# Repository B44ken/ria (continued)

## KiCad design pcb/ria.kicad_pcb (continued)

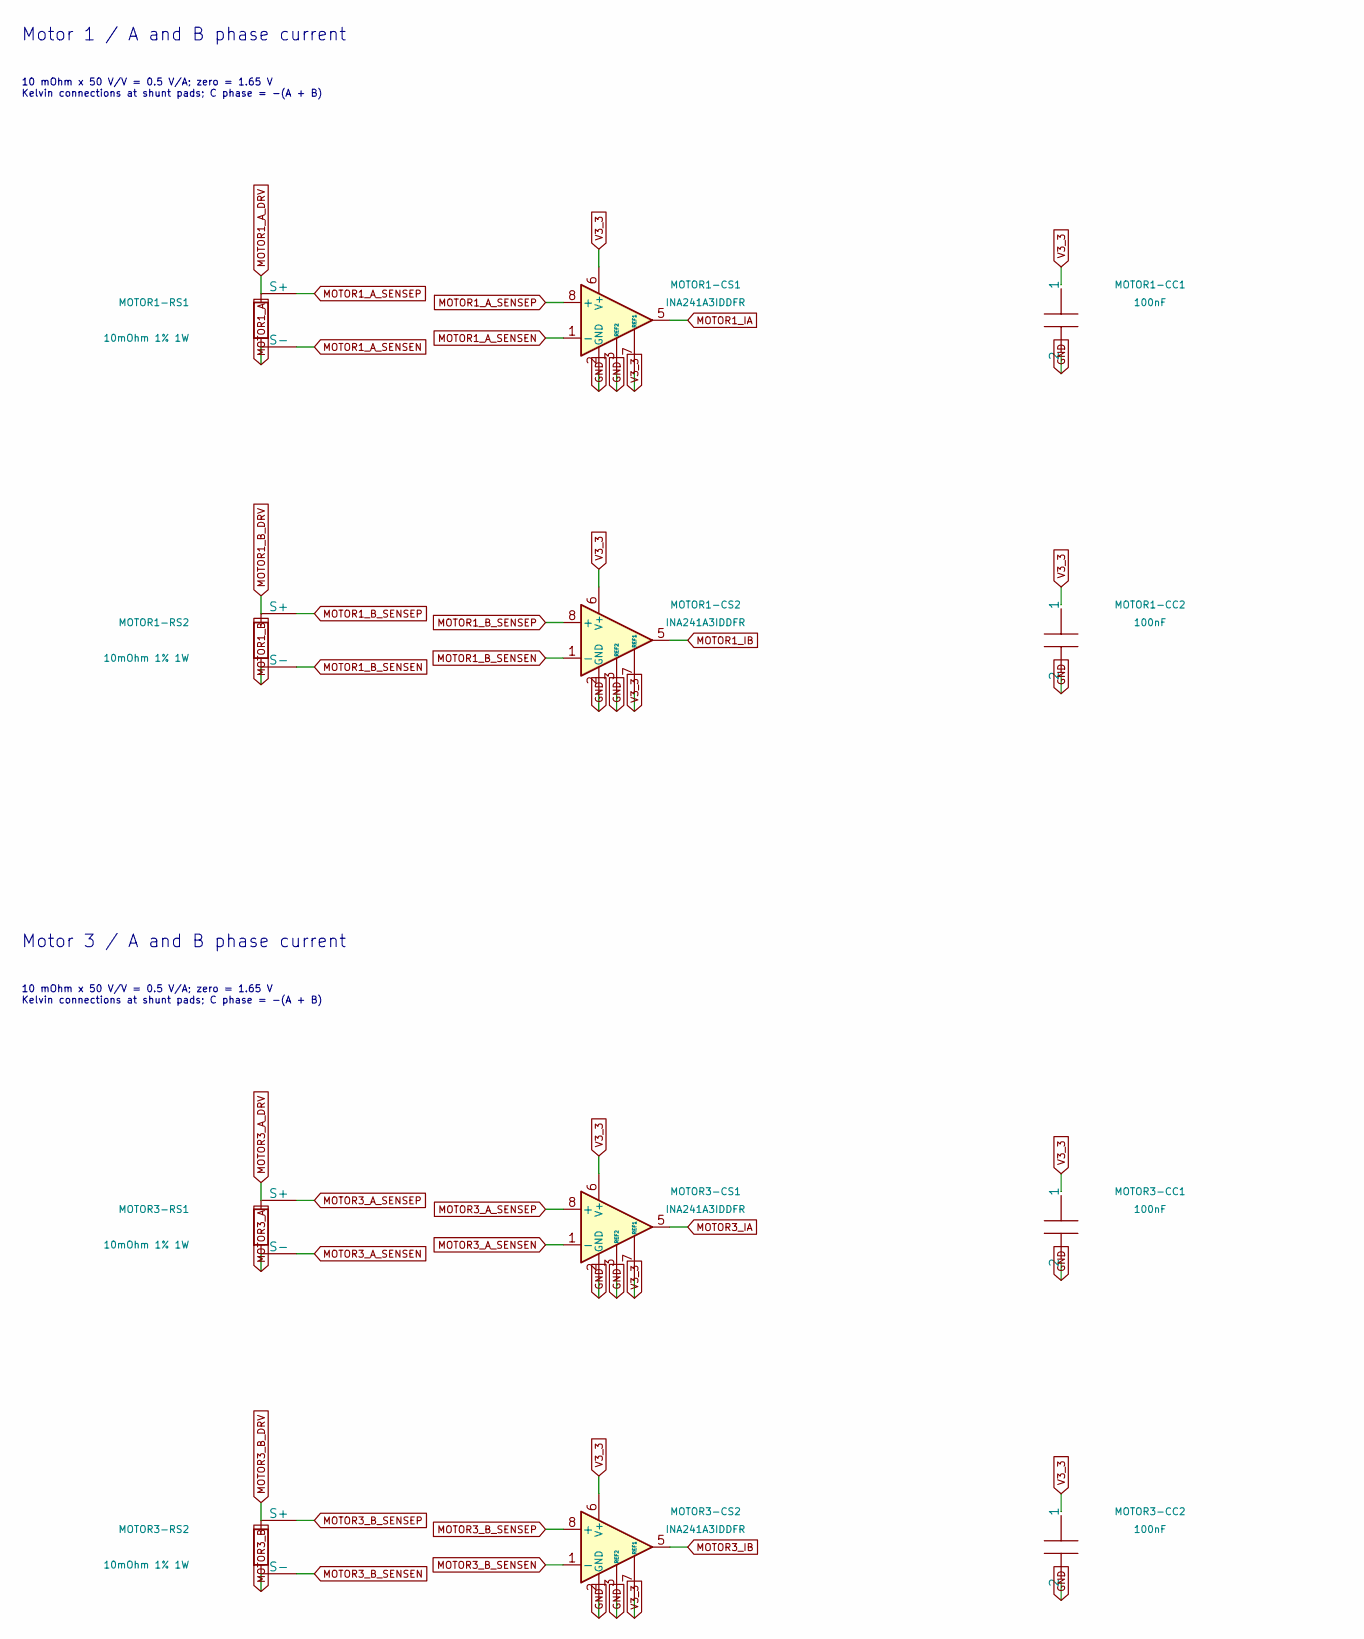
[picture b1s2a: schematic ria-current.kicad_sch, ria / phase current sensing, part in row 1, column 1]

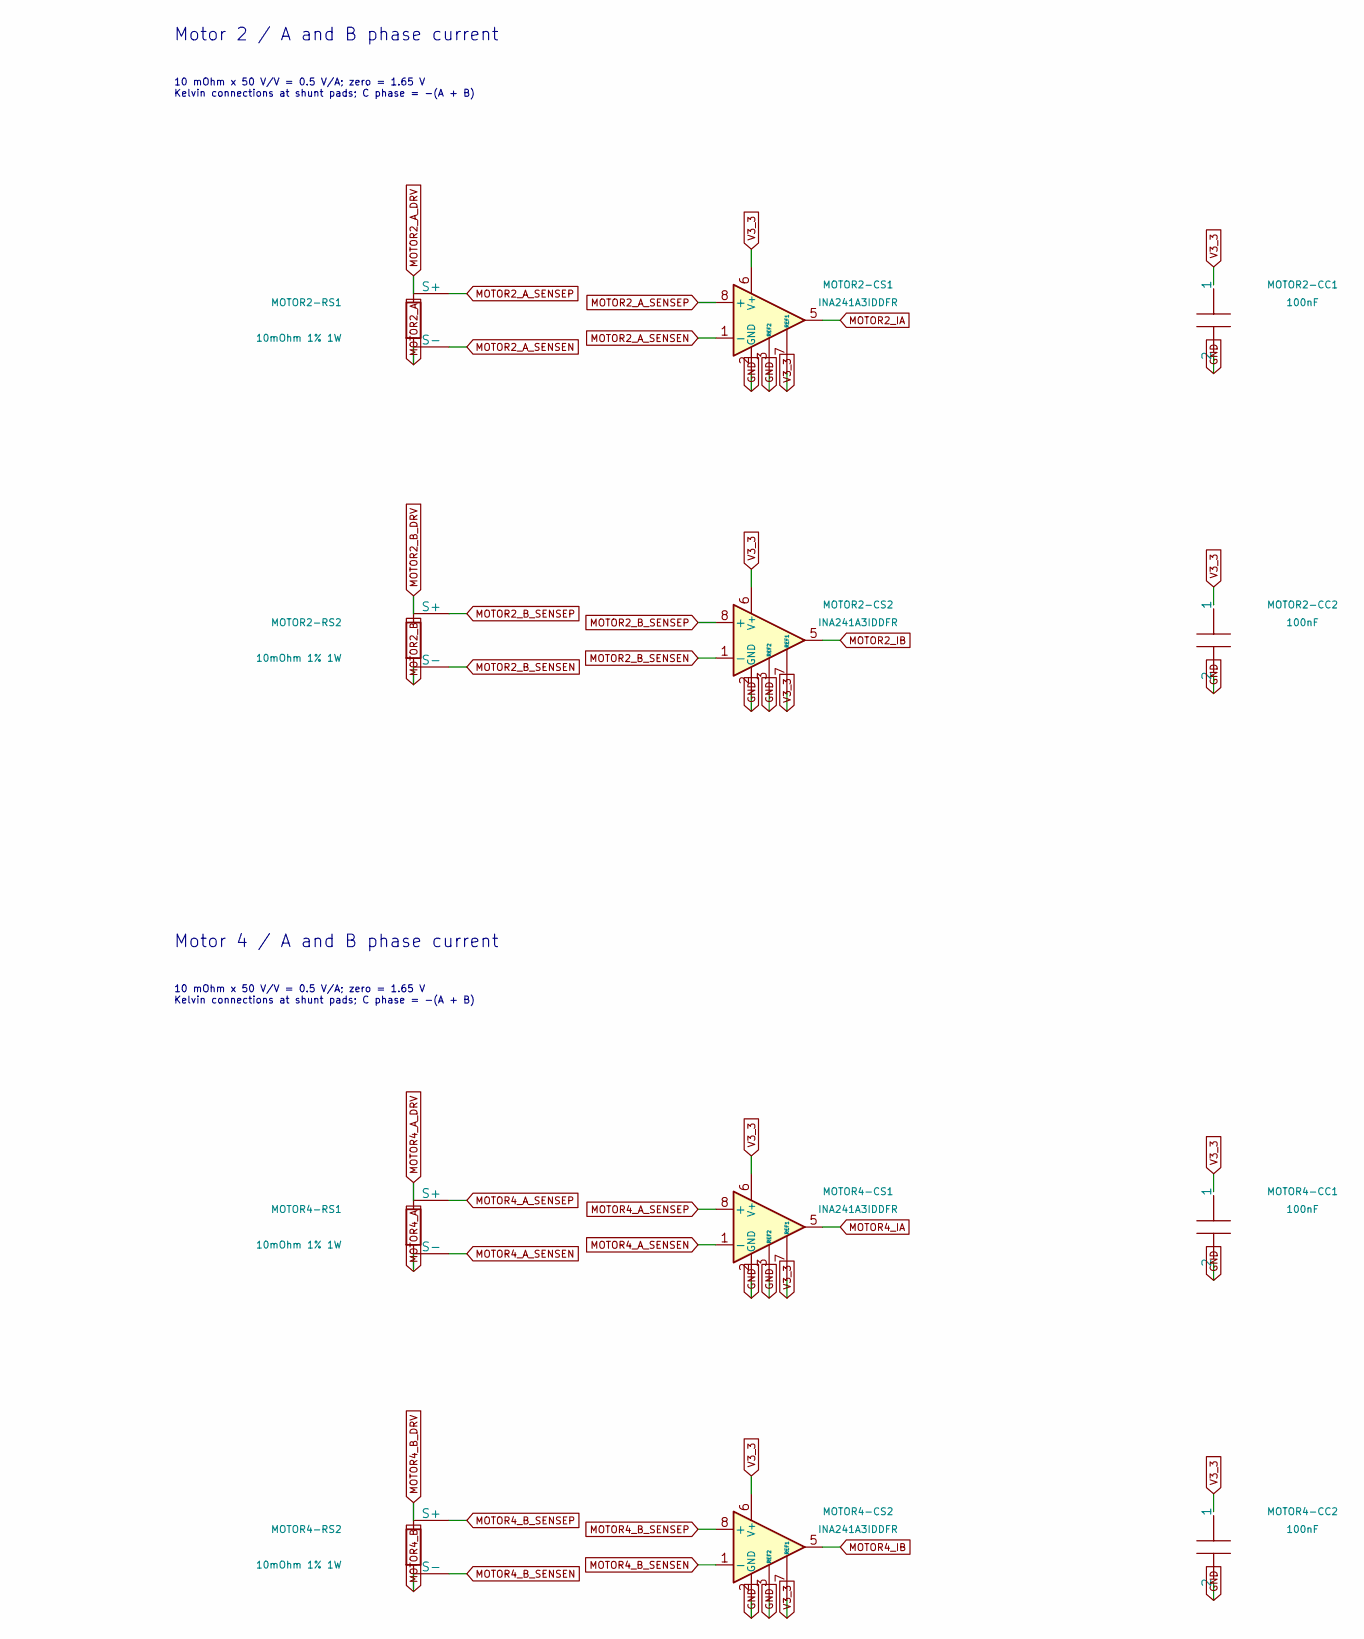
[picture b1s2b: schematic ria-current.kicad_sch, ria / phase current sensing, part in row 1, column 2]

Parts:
MOTOR1-CC1, MOTOR1-CC2, MOTOR2-CC1, MOTOR2-CC2, MOTOR3-CC1, MOTOR3-CC2, MOTOR4-CC1, MOTOR4-CC2: 100nF; C_0603_CURRENT; MPN CC0603KRX7R9BB104; LCSC C14663
MOTOR1-CS1, MOTOR1-CS2, MOTOR2-CS1, MOTOR2-CS2, MOTOR3-CS1, MOTOR3-CS2, MOTOR4-CS1, MOTOR4-CS2: INA241A3IDDFR; INA241A3_DDF; MPN INA241A3IDDFR; LCSC C6051860
MOTOR1-RS1, MOTOR1-RS2, MOTOR2-RS1, MOTOR2-RS2, MOTOR3-RS1, MOTOR3-RS2, MOTOR4-RS1, MOTOR4-RS2: 10mOhm 1% 1W; SHUNT_1206_KELVIN; MPN SMR12M1FR010T; LCSC C2692042

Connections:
GND: MOTOR1-CC1.2, MOTOR1-CC2.2, MOTOR1-CS1.2 (GND), MOTOR1-CS1.3 (REF2), MOTOR1-CS1.4 (GND), MOTOR1-CS2.2 (GND), MOTOR1-CS2.3 (REF2), MOTOR1-CS2.4 (GND), MOTOR2-CC1.2, MOTOR2-CC2.2, MOTOR2-CS1.2 (GND), MOTOR2-CS1.3 (REF2), MOTOR2-CS1.4 (GND), MOTOR2-CS2.2 (GND), MOTOR2-CS2.3 (REF2), MOTOR2-CS2.4 (GND), MOTOR3-CC1.2, MOTOR3-CC2.2, MOTOR3-CS1.2 (GND), MOTOR3-CS1.3 (REF2), MOTOR3-CS1.4 (GND), MOTOR3-CS2.2 (GND), MOTOR3-CS2.3 (REF2), MOTOR3-CS2.4 (GND), MOTOR4-CC1.2, MOTOR4-CC2.2, MOTOR4-CS1.2 (GND), MOTOR4-CS1.3 (REF2), MOTOR4-CS1.4 (GND), MOTOR4-CS2.2 (GND), MOTOR4-CS2.3 (REF2), MOTOR4-CS2.4 (GND); also elsewhere on the board
MOTOR1_A: MOTOR1-RS1.2; also elsewhere on the board
MOTOR1_A_DRV: MOTOR1-RS1.1; also elsewhere on the board
MOTOR1_A_SENSEN: MOTOR1-CS1.1 (-), MOTOR1-RS1.4 (S-)
MOTOR1_A_SENSEP: MOTOR1-CS1.8 (+), MOTOR1-RS1.3 (S+)
MOTOR1_B: MOTOR1-RS2.2; also elsewhere on the board
MOTOR1_B_DRV: MOTOR1-RS2.1; also elsewhere on the board
MOTOR1_B_SENSEN: MOTOR1-CS2.1 (-), MOTOR1-RS2.4 (S-)
MOTOR1_B_SENSEP: MOTOR1-CS2.8 (+), MOTOR1-RS2.3 (S+)
MOTOR1_IA: MOTOR1-CS1.5; also elsewhere on the board
MOTOR1_IB: MOTOR1-CS2.5; also elsewhere on the board
MOTOR2_A: MOTOR2-RS1.2; also elsewhere on the board
MOTOR2_A_DRV: MOTOR2-RS1.1; also elsewhere on the board
MOTOR2_A_SENSEN: MOTOR2-CS1.1 (-), MOTOR2-RS1.4 (S-)
MOTOR2_A_SENSEP: MOTOR2-CS1.8 (+), MOTOR2-RS1.3 (S+)
MOTOR2_B: MOTOR2-RS2.2; also elsewhere on the board
MOTOR2_B_DRV: MOTOR2-RS2.1; also elsewhere on the board
MOTOR2_B_SENSEN: MOTOR2-CS2.1 (-), MOTOR2-RS2.4 (S-)
MOTOR2_B_SENSEP: MOTOR2-CS2.8 (+), MOTOR2-RS2.3 (S+)
MOTOR2_IA: MOTOR2-CS1.5; also elsewhere on the board
MOTOR2_IB: MOTOR2-CS2.5; also elsewhere on the board
MOTOR3_A: MOTOR3-RS1.2; also elsewhere on the board
MOTOR3_A_DRV: MOTOR3-RS1.1; also elsewhere on the board
MOTOR3_A_SENSEN: MOTOR3-CS1.1 (-), MOTOR3-RS1.4 (S-)
MOTOR3_A_SENSEP: MOTOR3-CS1.8 (+), MOTOR3-RS1.3 (S+)
MOTOR3_B: MOTOR3-RS2.2; also elsewhere on the board
MOTOR3_B_DRV: MOTOR3-RS2.1; also elsewhere on the board
MOTOR3_B_SENSEN: MOTOR3-CS2.1 (-), MOTOR3-RS2.4 (S-)
MOTOR3_B_SENSEP: MOTOR3-CS2.8 (+), MOTOR3-RS2.3 (S+)
MOTOR3_IA: MOTOR3-CS1.5; also elsewhere on the board
MOTOR3_IB: MOTOR3-CS2.5; also elsewhere on the board
MOTOR4_A: MOTOR4-RS1.2; also elsewhere on the board
MOTOR4_A_DRV: MOTOR4-RS1.1; also elsewhere on the board
MOTOR4_A_SENSEN: MOTOR4-CS1.1 (-), MOTOR4-RS1.4 (S-)
MOTOR4_A_SENSEP: MOTOR4-CS1.8 (+), MOTOR4-RS1.3 (S+)
MOTOR4_B: MOTOR4-RS2.2; also elsewhere on the board
MOTOR4_B_DRV: MOTOR4-RS2.1; also elsewhere on the board
MOTOR4_B_SENSEN: MOTOR4-CS2.1 (-), MOTOR4-RS2.4 (S-)
MOTOR4_B_SENSEP: MOTOR4-CS2.8 (+), MOTOR4-RS2.3 (S+)
MOTOR4_IA: MOTOR4-CS1.5; also elsewhere on the board
MOTOR4_IB: MOTOR4-CS2.5; also elsewhere on the board
V3_3: MOTOR1-CC1.1, MOTOR1-CC2.1, MOTOR1-CS1.6 (V+), MOTOR1-CS1.7 (REF1), MOTOR1-CS2.6 (V+), MOTOR1-CS2.7 (REF1), MOTOR2-CC1.1, MOTOR2-CC2.1, MOTOR2-CS1.6 (V+), MOTOR2-CS1.7 (REF1), MOTOR2-CS2.6 (V+), MOTOR2-CS2.7 (REF1), MOTOR3-CC1.1, MOTOR3-CC2.1, MOTOR3-CS1.6 (V+), MOTOR3-CS1.7 (REF1), MOTOR3-CS2.6 (V+), MOTOR3-CS2.7 (REF1), MOTOR4-CC1.1, MOTOR4-CC2.1, MOTOR4-CS1.6 (V+), MOTOR4-CS1.7 (REF1), MOTOR4-CS2.6 (V+), MOTOR4-CS2.7 (REF1); also elsewhere on the board

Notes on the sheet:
Motor 1 / A and B phase current
10 mOhm x 50 V/V = 0.5 V/A; zero = 1.65 V Kelvin connections at shunt pads; C phase = -(A + B)
Motor 2 / A and B phase current
Motor 3 / A and B phase current
Motor 4 / A and B phase current

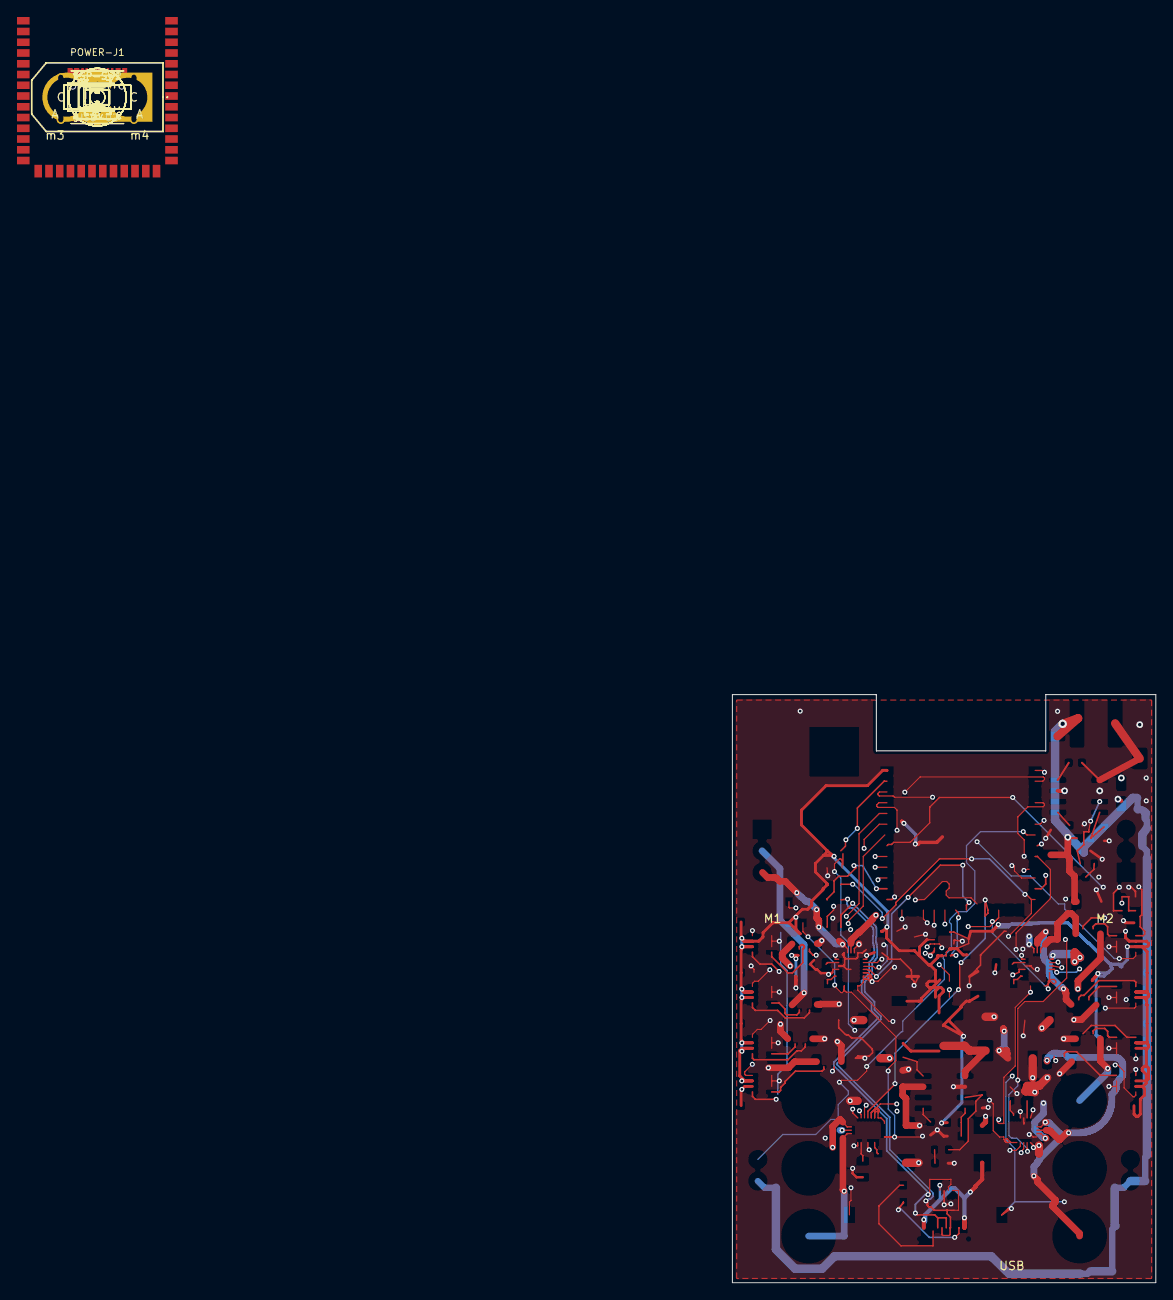
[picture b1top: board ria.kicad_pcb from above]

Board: 4 copper layers, 50.0 x 69.5 mm, 107 parts (0 on the bottom side), 98 nets.

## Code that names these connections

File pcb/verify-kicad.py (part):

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        for window in windows:
            assert not window.GetEffectiveShape(pcbnew.F_Paste).Collide(via.GetEffectiveHoleShape(), 0)
    for pin in [9, 10, 11]:
        assert pin_nets[ref, str(pin)] == "BAT"
    for pin in [2, 4, 12, 15, 18, 21, 24, 26, 34, 35, 41]:
        assert pin_nets[ref, str(pin)] == "GND"
    for pin in [25, 28, 30, 32, 37]:
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    for outputs, phase in zip([(13, 14), (16, 17), (19, 20)], "ABC"):
        for output in outputs:
            assert pin_nets[ref, str(output)] == prefix + f"_{phase}"
    assert pin_nets[ref, "23"] == "MOTOR_ENABLE"
    assert pin_nets[ref, "22"] == prefix + "_FAULT"
    assert pin_nets[prefix + "-R3", "1"] == prefix + "_AVDD"
    assert pin_nets[prefix + "-R3", "2"] == prefix + "_FAULT"
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    assert footprints[prefix + "-R1"].GetValue() == "47kΩ"
    assert pin_nets[prefix + "-R1", "1"] == prefix + "_AVDD"
    assert pcb_nets[prefix + "_CP"] == {(ref, "8"), (prefix + "-C2", "1")}
    assert pin_nets[prefix + "-C2", "2"] == "BAT"
    assert footprints[prefix + "-C2"].GetValue() == "1uF"
    assert pcb_nets[prefix + "_CPH"] == {(ref, "7"), (prefix + "-C7", "1")}
    assert pcb_nets[prefix + "_CPL"] == {(ref, "6"), (prefix + "-C7", "2")}
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        assert component.findtext("fields/field[@name='MPN']") == mpn
        description = component.findtext("fields/field[@name='Description']")
        assert "50V" in description and "X7R" in description
        assert pin_nets[capacitor, "1"] == "BAT"
        assert pin_nets[capacitor, "2"] == "GND"
    for pin, phase, resistor, capacitor in [(40, "A", "R4", "C11"), (39, "B", "R5", "C12")]:
        raw = prefix + f"_ISENSE_{phase}_RAW"
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assert pin_nets["ESP-U1", "33"] == "IMU_SDA"
assert pin_nets["ESP-U1", "34"] == "IMU_SCL"
assert pin_nets["ESP-U1", "18"] == "VBAT_SENSE"
assert pin_nets["SENSE-R1", "1"] == "BAT"
assert pin_nets["SENSE-R1", "2"] == "VBAT_SENSE"
assert pin_nets["SENSE-R2", "1"] == "VBAT_SENSE"
assert pin_nets["SENSE-R2", "2"] == "GND"
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assert footprints["SENSE-C1"].GetValue() == "100nF"
for pin in [15, 16, 26, 37]:
    assert ("ESP-U1", str(pin)) not in pin_nets
assert pin_nets["ESP-U1", "13"] == "ESP_USB_DM"
assert pin_nets["ESP-U1", "14"] == "ESP_USB_DP"
assert pin_nets["ESP-U1", "24"] == "MOTOR_ENABLE"
assert pin_nets["ESP-U1", "27"] == "ESP_BOOT"
assert not {"MOTOR_MISO", "MOTOR_MOSI", "MOTOR_SCLK", "MOTOR_FAULT", "SDA0", "SCL0"} & pcb_nets.keys()
assert board.GetCopperLayerCount() == 4
board_outline = pcbnew.SHAPE_POLY_SET()
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power_pads = {pad.GetNumber(): pad for pad in xt60.Pads()}
assert power_pads.keys() == {"1", "2"}
assert pin_nets["POWER-J1", "1"] == "GND"
assert pin_nets["POWER-J1", "2"] == "BAT"
negative, positive = power_pads["1"], power_pads["2"]
assert positive.GetPosition().x - negative.GetPosition().x == pcbnew.FromMM(7.2)
assert positive.GetPosition().y == negative.GetPosition().y
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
